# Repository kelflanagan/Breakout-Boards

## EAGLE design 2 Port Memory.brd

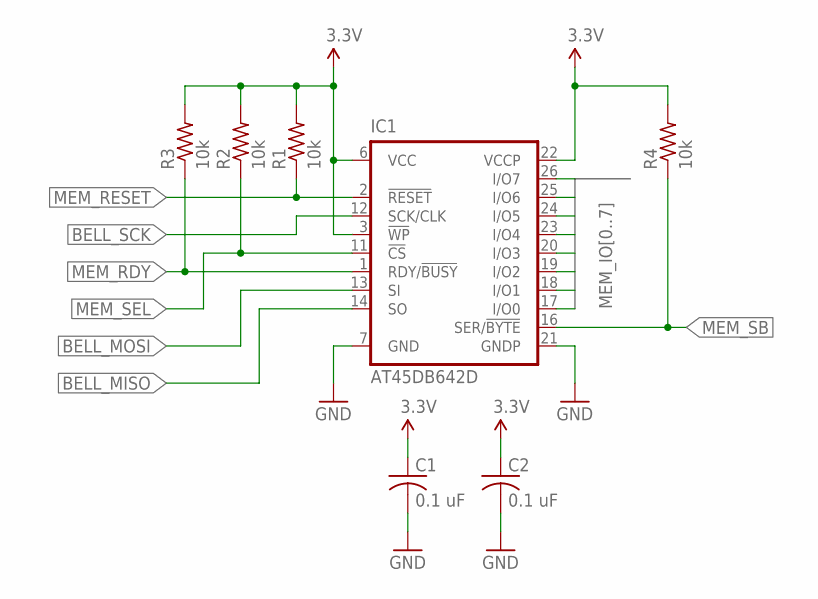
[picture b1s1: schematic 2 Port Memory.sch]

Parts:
C1, C2: 0.1 uF; 0603_CAP; DIGIKEY# 399-1096-1-ND
IC1: AT45DB642D; 28T-TSOP-1
R1, R2, R3, R4: 10k; 0603_RESISTOR; DIGIKEY# P10KGCT-ND

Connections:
3.3V: C1.1, C2.1, IC1.3 (!WP), IC1.6 (VCC), IC1.22 (VCCP), R1.2, R2.2, R3.2, R4.2
BELL_MISO: IC1.14 (SO)
BELL_MOSI: IC1.13 (SI)
BELL_SCK: IC1.12 (SCK/CLK)
GND: C1.2, C2.2, IC1.7 (GND), IC1.21 (GNDP)
MEM_IO0: IC1.17 (I/O0)
MEM_IO1: IC1.18 (I/O1)
MEM_IO2: IC1.19 (I/O2)
MEM_IO3: IC1.20 (I/O3)
MEM_IO4: IC1.23 (I/O4)
MEM_IO5: IC1.24 (I/O5)
MEM_IO6: IC1.25 (I/O6)
MEM_IO7: IC1.26 (I/O7)
MEM_RDY: IC1.1 (RDY/!BUSY), R3.1
MEM_RESET: IC1.2 (!RESET), R1.1
MEM_SB: IC1.16 (SER/!BYTE), R4.1
MEM_SEL: IC1.11 (!CS), R2.1

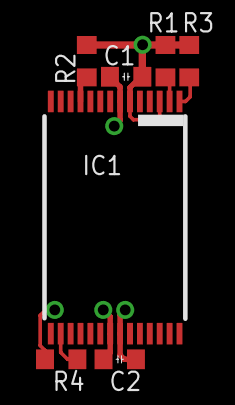
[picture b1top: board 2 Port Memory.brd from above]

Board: 4 copper layers, 7 parts (0 on the bottom side), 6 nets.

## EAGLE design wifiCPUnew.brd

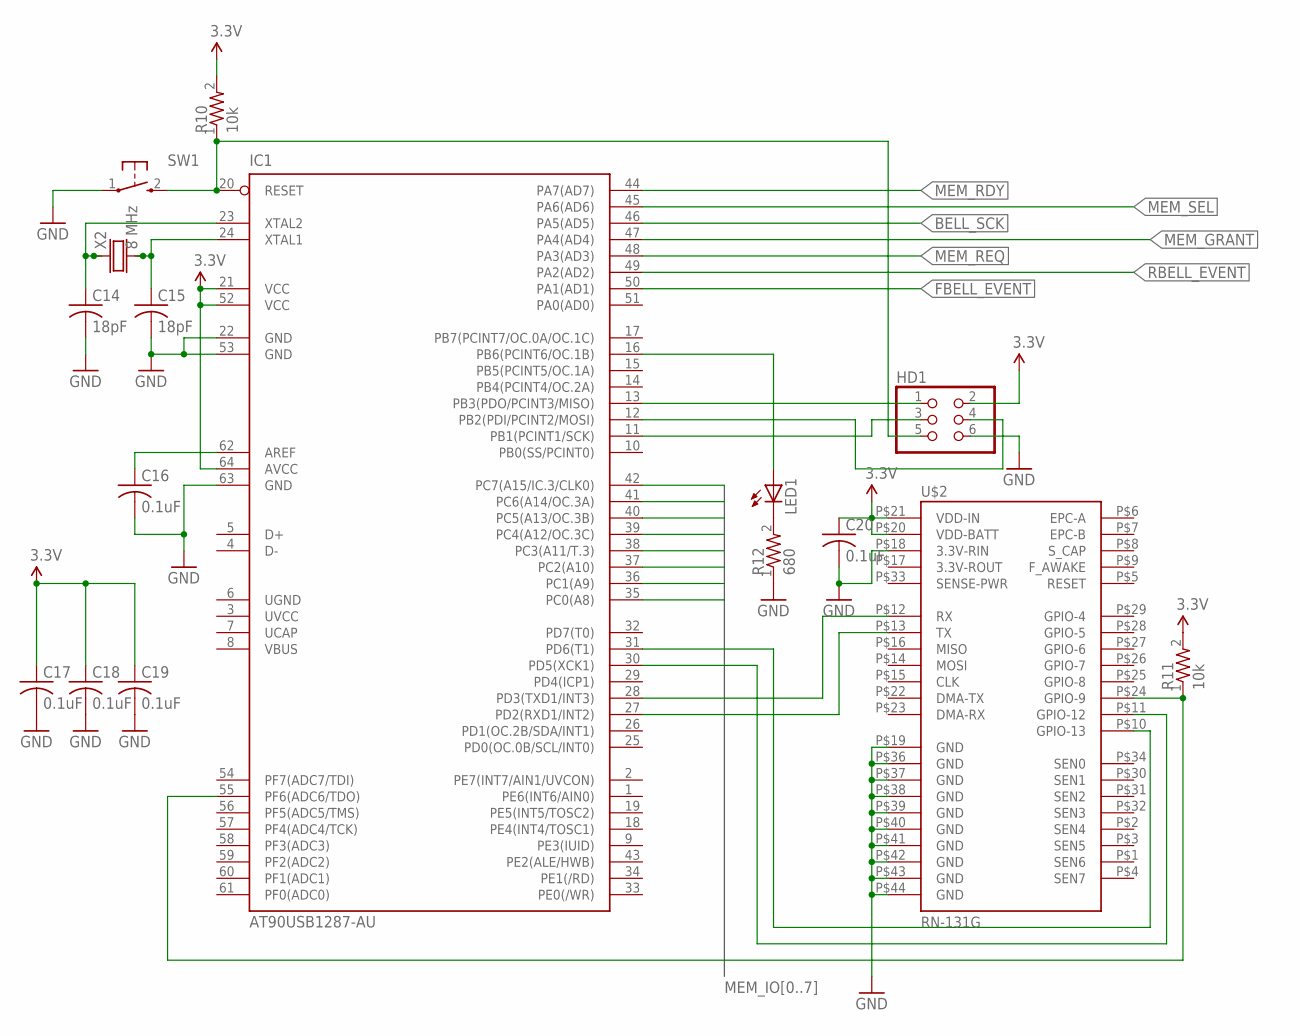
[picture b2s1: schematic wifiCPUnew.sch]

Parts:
C14, C15: 18pF; 0603_RESISTOR
C16, C17, C18, C19, C20: 0.1uF; 0603_RESISTOR
HD1: HEADER2X3
IC1: AT90USB1287-AU; TQFP64
LED1: LEDCHIP-LED0603; CHIP-LED0603
R10, R11: 10k; 0603_RESISTOR
R12: 680; 0603_RESISTOR
SW1: TAC-SWITCH
U$2: RN-131G
X2: 8 MHz; CRYSTAL_5X3

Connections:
3.3V: C17.1, C18.1, C19.1, C20.1, HD1.2, IC1.21 (VCC), IC1.52 (VCC), IC1.64 (AVCC), R10.2, R11.2, U$2.P$20 (VDD-BATT), U$2.P$21 (VDD-IN)
BELL_SCK: IC1.46 (PA5(AD5))
FBELL_EVENT: IC1.50 (PA1(AD1))
GND: C14.2, C15.2, C16.2, C17.2, C18.2, C19.2, C20.2, HD1.6, IC1.22 (GND), IC1.53 (GND), IC1.63 (GND), R12.1, SW1.1, U$2.P$18 (3.3V-RIN), U$2.P$19 (GND), U$2.P$36 (GND), U$2.P$37 (GND), U$2.P$38 (GND), U$2.P$39 (GND), U$2.P$40 (GND), U$2.P$41 (GND), U$2.P$42 (GND), U$2.P$43 (GND), U$2.P$44 (GND)
MEM_GRANT: IC1.47 (PA4(AD4))
MEM_IO0: IC1.35 (PC0(A8))
MEM_IO1: IC1.36 (PC1(A9))
MEM_IO2: IC1.37 (PC2(A10))
MEM_IO3: IC1.38 (PC3(A11/T.3))
MEM_IO4: IC1.39 (PC4(A12/OC.3C))
MEM_IO5: IC1.40 (PC5(A13/OC.3B))
MEM_IO6: IC1.41 (PC6(A14/OC.3A))
MEM_IO7: IC1.42 (PC7(A15/IC.3/CLK0))
MEM_RDY: IC1.44 (PA7(AD7))
MEM_REQ: IC1.48 (PA3(AD3))
MEM_SEL: IC1.45 (PA6(AD6))
MISO: HD1.1, IC1.13 (PB3(PDO/PCINT3/MISO))
MOSI: HD1.4, IC1.12 (PB2(PDI/PCINT2/MOSI))
unnamed: C14.1, IC1.23 (XTAL2), X2.1
unnamed: C15.1, IC1.24 (XTAL1), X2.2
unnamed: LED1.C, R12.2
unnamed: IC1.16 (PB6(PCINT6/OC.1B)), LED1.A
unnamed: IC1.28 (PD3(TXD1/INT3)), U$2.P$12 (RX)
unnamed: C16.1, IC1.62 (AREF)
unnamed: IC1.27 (PD2(RXD1/INT2)), U$2.P$13 (TX)
unnamed: IC1.31 (PD6(T1)), U$2.P$10 (GPIO-13)
unnamed: IC1.30 (PD5(XCK1)), U$2.P$11 (GPIO-12)
unnamed: IC1.55 (PF6(ADC6/TDO)), R11.1, U$2.P$24 (GPIO-9)
RBELL_EVENT: IC1.49 (PA2(AD2))
SCK: HD1.3, IC1.11 (PB1(PCINT1/SCK))
UCAP: IC1.7 (UCAP)
UGND: IC1.6 (UGND)
UVCC: IC1.3 (UVCC)
VBUS: IC1.8 (VBUS)
WIFI_RESET: HD1.5, IC1.20 (RESET), R10.1, SW1.2

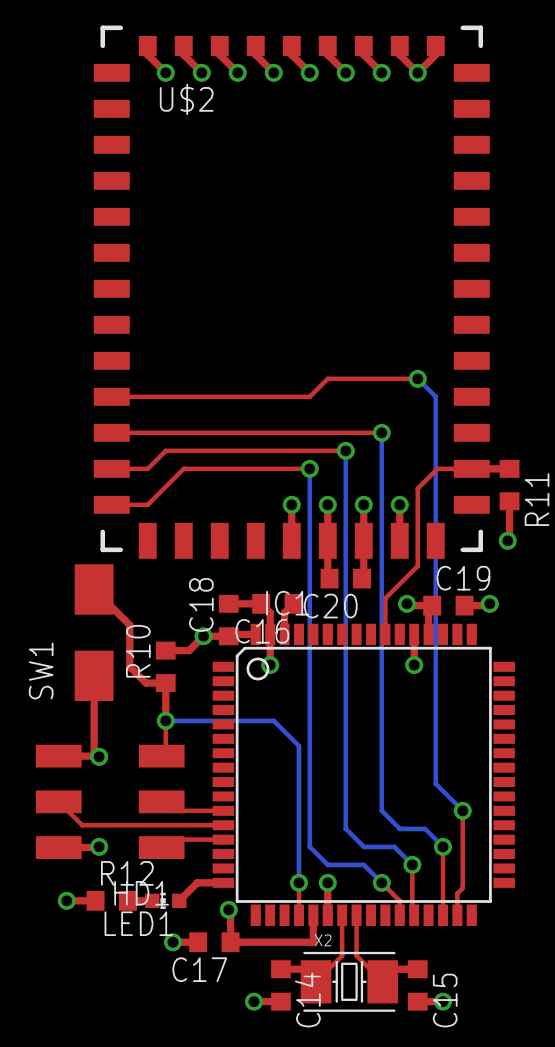
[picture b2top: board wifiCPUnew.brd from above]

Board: 4 copper layers, 16 parts (0 on the bottom side), 16 nets.

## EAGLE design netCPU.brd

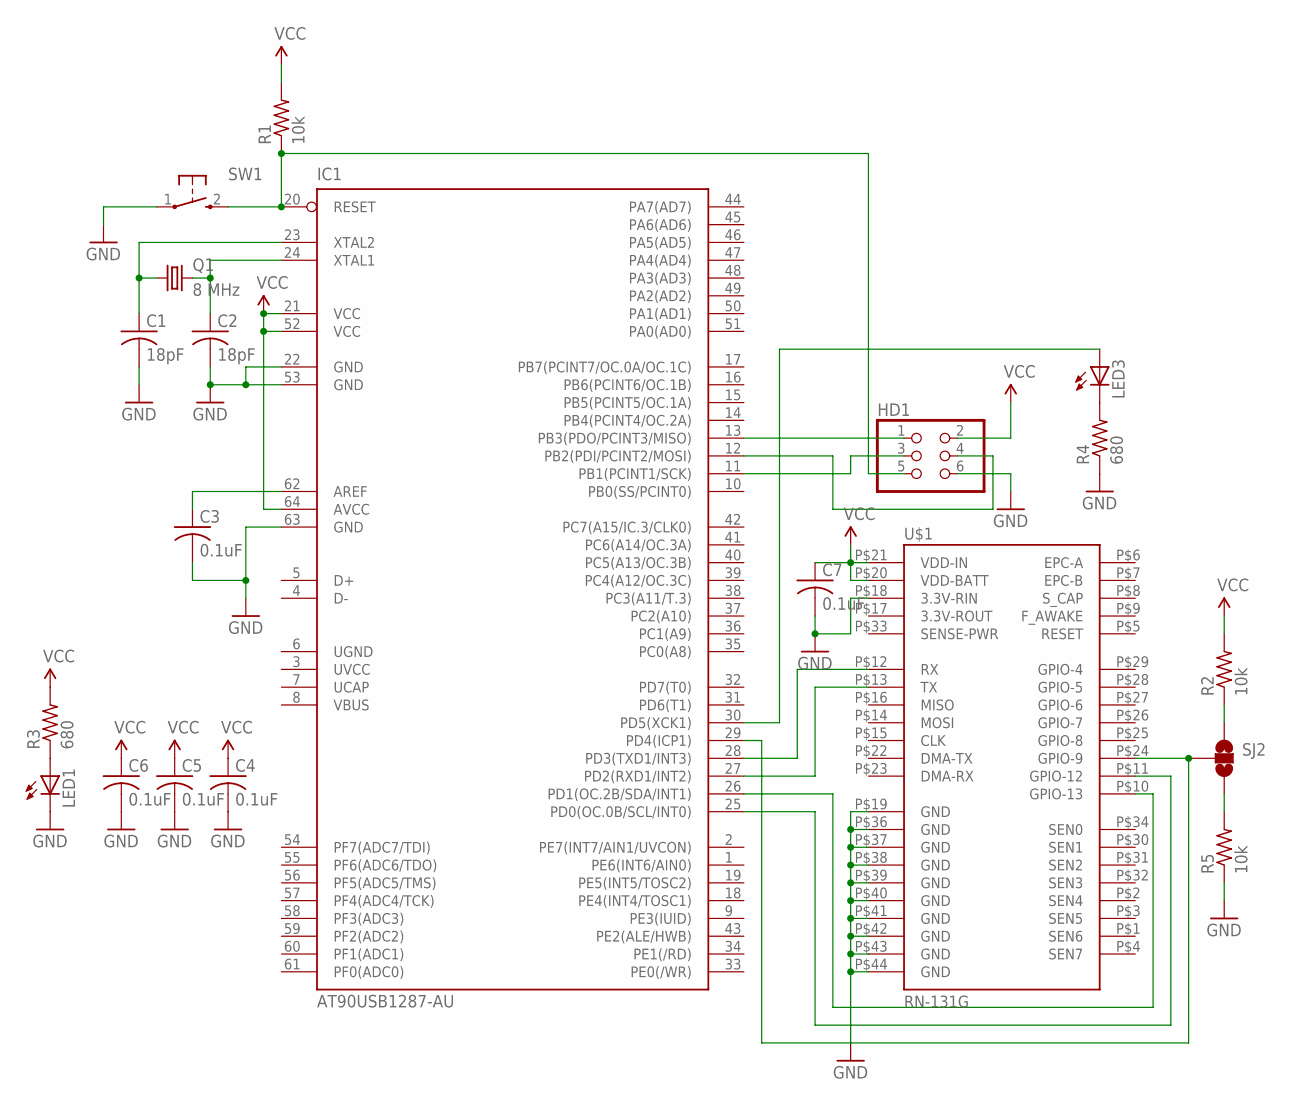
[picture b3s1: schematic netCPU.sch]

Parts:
C1, C2: 18pF; C0603K
C3, C4, C5, C6, C7: 0.1uF; C0603K
HD1: HEADER2X3
IC1: AT90USB1287-AU; TQFP64
LED1, LED3: LEDCHIP-LED0603; CHIP-LED0603
Q1: 8 MHz; HC49UP
R1, R2, R5: 10k; R0603
R3, R4: 680; R0603
SJ2: SOLDERJUMPER_2WAYPASTE2&3; SJ_3_PASTE2&3
SW1: TAC-SWITCH
U$1: RN-131G

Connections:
GND: C1.2, C2.2, C3.2, C4.2, C5.2, C6.2, C7.2, HD1.6, IC1.22 (GND), IC1.53 (GND), IC1.63 (GND), LED1.C, R4.1, R5.1, SW1.1, U$1.P$18 (3.3V-RIN), U$1.P$19 (GND), U$1.P$36 (GND), U$1.P$37 (GND), U$1.P$38 (GND), U$1.P$39 (GND), U$1.P$40 (GND), U$1.P$41 (GND), U$1.P$42 (GND), U$1.P$43 (GND), U$1.P$44 (GND)
unnamed: C1.1, IC1.23 (XTAL2), Q1.1
unnamed: C2.1, IC1.24 (XTAL1), Q1.2
unnamed: HD1.1, IC1.13 (PB3(PDO/PCINT3/MISO))
unnamed: HD1.5, IC1.20 (RESET), R1.1, SW1.2
unnamed: HD1.4, IC1.12 (PB2(PDI/PCINT2/MOSI))
unnamed: IC1.28 (PD3(TXD1/INT3)), U$1.P$12 (RX)
unnamed: HD1.3, IC1.11 (PB1(PCINT1/SCK))
unnamed: C3.1, IC1.62 (AREF)
unnamed: IC1.27 (PD2(RXD1/INT2)), U$1.P$13 (TX)
unnamed: IC1.26 (PD1(OC.2B/SDA/INT1)), U$1.P$10 (GPIO-13)
unnamed: IC1.25 (PD0(OC.0B/SCL/INT0)), U$1.P$11 (GPIO-12)
unnamed: LED1.A, R3.1
unnamed: IC1.29 (PD4(ICP1)), SJ2.2, U$1.P$24 (GPIO-9)
unnamed: LED3.C, R4.2
unnamed: IC1.30 (PD5(XCK1)), LED3.A
unnamed: R5.2, SJ2.3
unnamed: R2.1, SJ2.1
UCAP: IC1.7 (UCAP)
UGND: IC1.6 (UGND)
UVCC: IC1.3 (UVCC)
VBUS: IC1.8 (VBUS)
VCC: C4.1, C5.1, C6.1, C7.1, HD1.2, IC1.21 (VCC), IC1.52 (VCC), IC1.64 (AVCC), R1.2, R2.2, R3.2, U$1.P$20 (VDD-BATT), U$1.P$21 (VDD-IN)

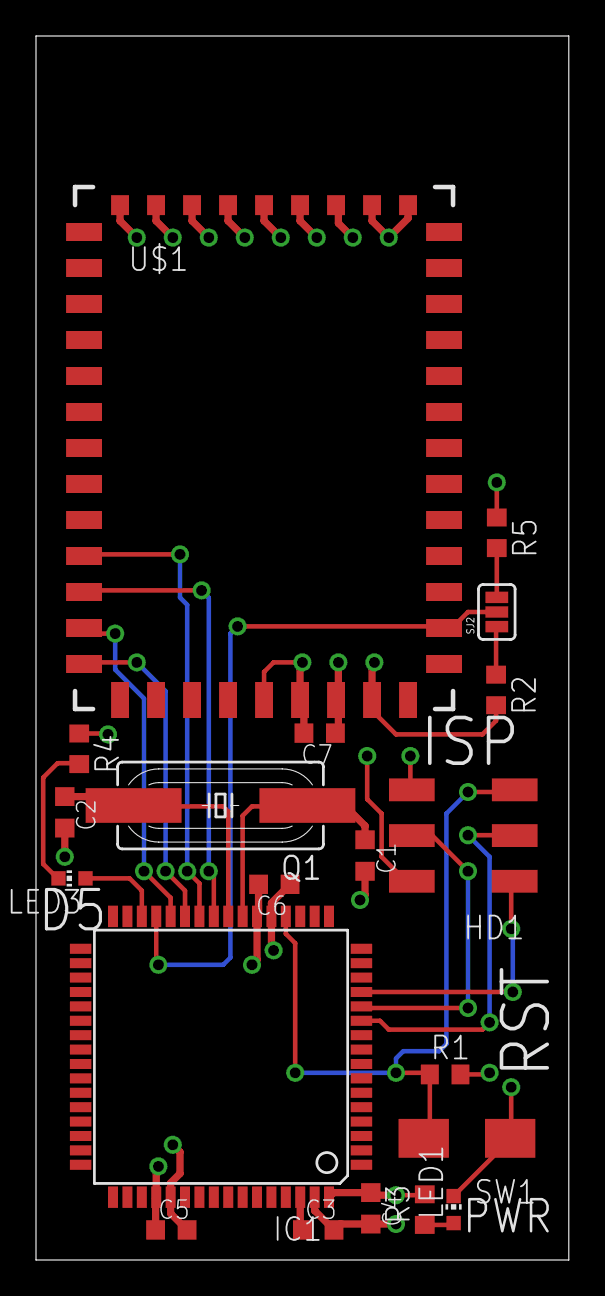
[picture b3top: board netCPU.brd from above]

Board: 4 copper layers, 29.6 x 68.0 mm, 20 parts (0 on the bottom side), 19 nets.

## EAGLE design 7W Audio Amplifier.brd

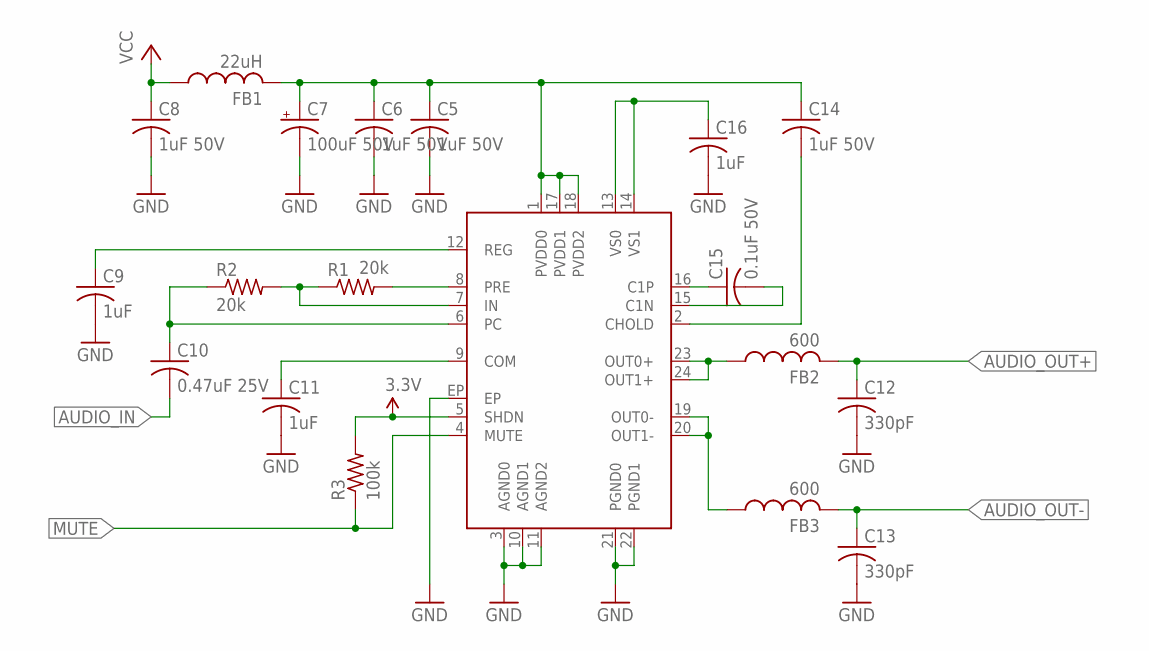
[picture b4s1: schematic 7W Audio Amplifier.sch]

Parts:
C5, C6, C8, C14: 1uF 50V; 0805_CAP; DIGIKEY# 445-7547-1-ND
C7: 100uF 50V; F_CAP; DIGIKEY# PCE3917CT-ND
C9, C11, C16: 1uF; 0603_CAP; DIGIKEY# 445-5138-1-ND
C10: 0.47uF 25V; 0603_CAP; DIGIKEY# 445-7418-1-ND
C12, C13: 330pF; 0603_CAP; DIGIKEY# 445-5074-1-ND
C15: 0.1uF 50V; 0603_CAP; DIGIKEY# 445-1314-1-ND
FB1: 22uH; 0805_FB; DIGIKEY# 490-5987-1-ND
FB2, FB3: 600; 0805_FB; DIGIKEY# 445-2206-1-ND
MAX1: MAX9737; TQFN24
R1, R2: 20k; 0603_RESISTOR; DIGIKEY# RHM20.0KCFCT-ND
R3: 100k; 0603_RESISTOR; DIGIKEY# 311-100KGRCT-ND

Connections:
3.3V: MAX1.5 (SHDN), R3.2
AUDIO_IN: C10.2
AUDIO_OUT+: C12.1, FB2.2
AUDIO_OUT-: C13.1, FB3.2
GND: C5.2, C6.2, C7.-, C8.2, C9.2, C11.2, C12.2, C13.2, C16.2, MAX1.3 (AGND0), MAX1.10 (AGND1), MAX1.11 (AGND2), MAX1.21 (PGND0), MAX1.22 (PGND1), MAX1.EP
MUTE: MAX1.4 (MUTE), R3.1
unnamed: C9.1, MAX1.12 (REG)
unnamed: MAX1.8 (PRE), R1.2
unnamed: C5.1, C6.1, C7.+, C14.1, FB1.2, MAX1.1 (PVDD0), MAX1.17 (PVDD1), MAX1.18 (PVDD2)
unnamed: MAX1.7 (IN), R1.1, R2.2
unnamed: C10.1, MAX1.6 (PC), R2.1
unnamed: C11.1, MAX1.9 (COM)
unnamed: C14.2, MAX1.2 (CHOLD)
unnamed: C15.1, MAX1.16 (C1P)
unnamed: C15.2, MAX1.15 (C1N)
unnamed: C16.1, MAX1.13 (VS0), MAX1.14 (VS1)
unnamed: FB3.1, MAX1.19 (OUT0-), MAX1.20 (OUT1-)
unnamed: FB2.1, MAX1.23 (OUT0+), MAX1.24 (OUT1+)
VCC: C8.1, FB1.1

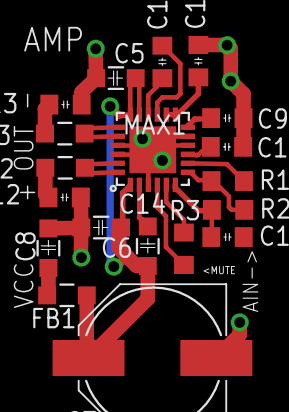
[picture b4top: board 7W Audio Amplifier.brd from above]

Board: 4 copper layers, 19 parts (0 on the bottom side), 18 nets.

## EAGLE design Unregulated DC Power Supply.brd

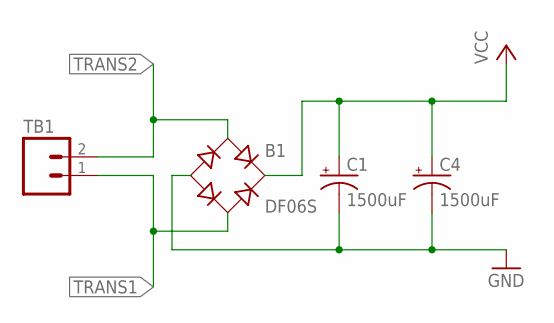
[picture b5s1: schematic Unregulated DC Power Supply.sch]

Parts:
B1: DF06S; DFS
C1, C4: 1500uF; CAP_J16
TB1: TERMINAL_BLOCK_2; TERMINL_BLOCK_2_POS

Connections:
GND: B1.-, C1.1 (-), C4.1 (-)
TRANS1: B1.AC2, TB1.1
TRANS2: B1.AC1, TB1.2
VCC: B1.+, C1.2 (+), C4.2 (+)

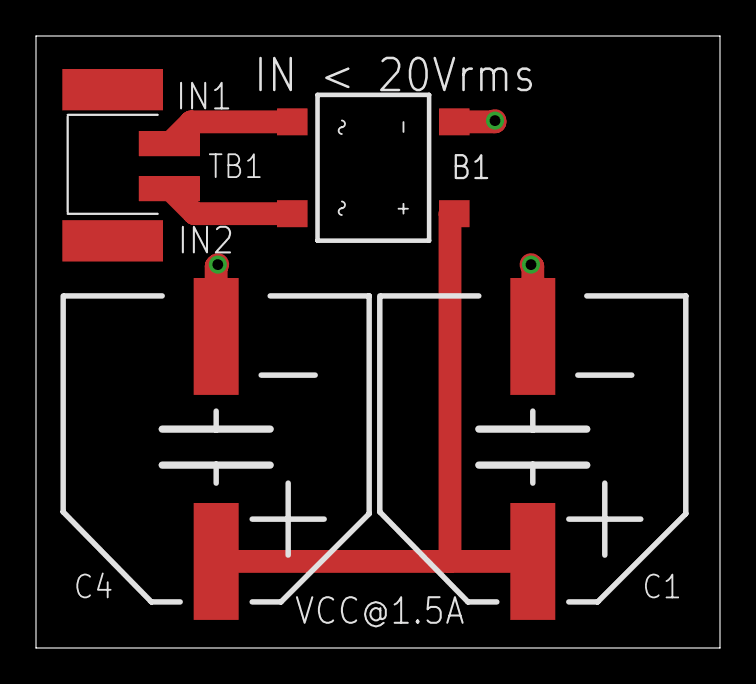
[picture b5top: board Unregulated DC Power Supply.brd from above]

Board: 4 copper layers, 38.0 x 34.0 mm, 4 parts (0 on the bottom side), 4 nets.

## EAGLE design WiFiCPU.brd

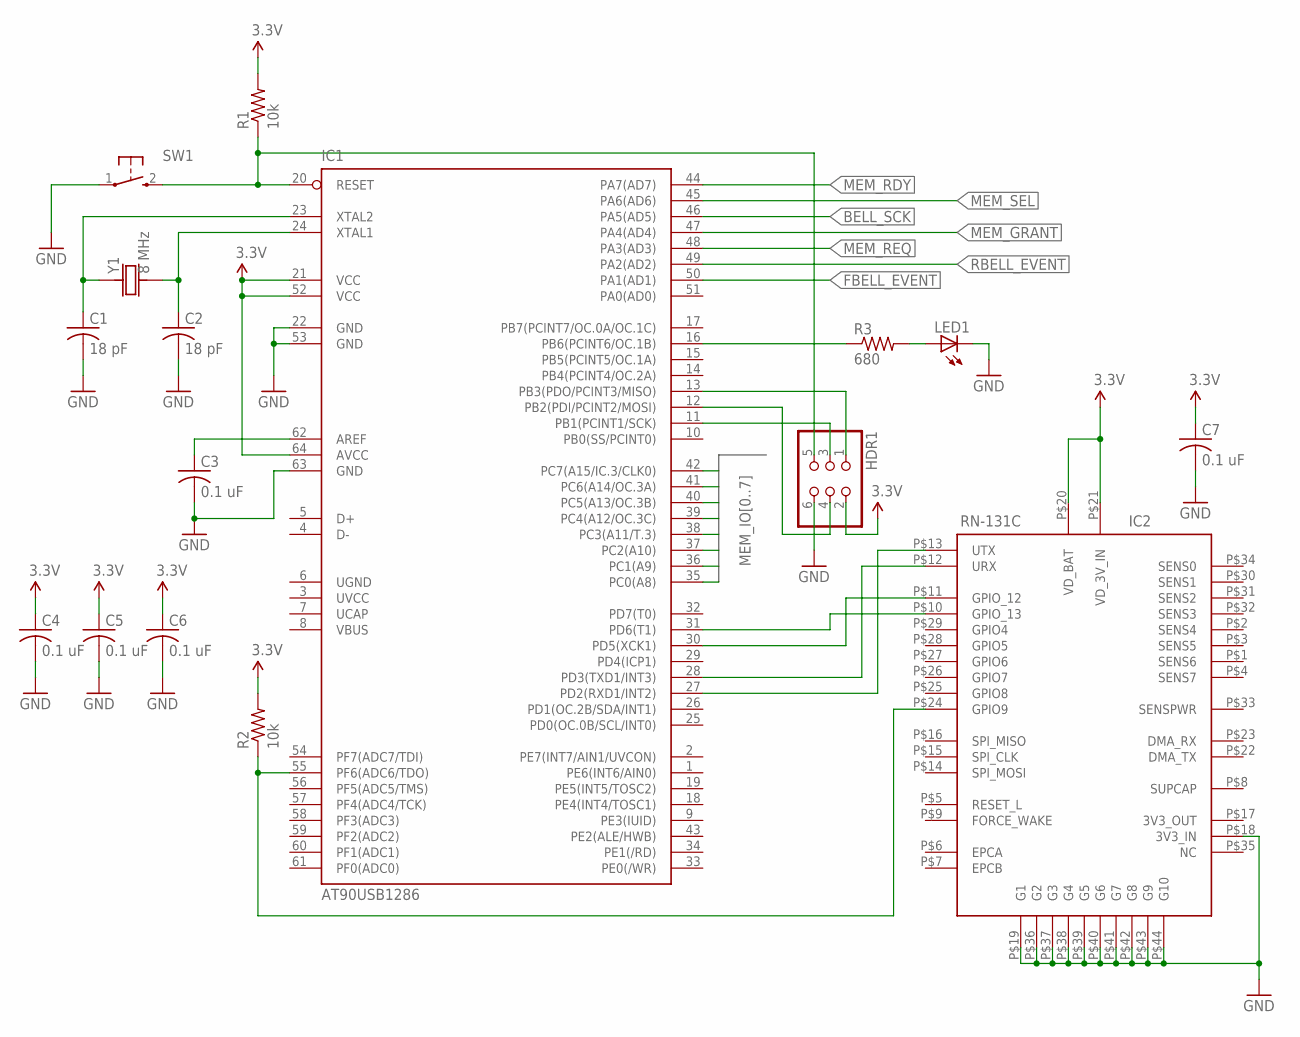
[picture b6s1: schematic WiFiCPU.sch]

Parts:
C1, C2: 18 pF; 0603_CAP; DIGIKEY# 399-1052-1-ND
C3, C4, C5, C6, C7: 0.1 uF; 0603_CAP; DIGIKEY# 399-1096-1-ND
HDR1: HEADER_2X3
IC1: AT90USB1286; TQFP64; DIGIKEY# AT90USB1286-AURCT-ND
IC2: RN-131C; RN-131G
LED1: LED0603; 0603_LED
R1, R2: 10k; 0603_RESISTOR; DIGIKEY# P10KGCT-ND
R3: 680; 0603_RESISTOR; DIGIKEY# P680GCT-ND
SW1: SWITCH; SWITCH_TAC
Y1: 8 MHz; CRYSTAL_5X3; DIGIKEY# 887-1448-1-ND

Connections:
3.3V: C4.1, C5.1, C6.1, C7.1, HDR1.2, IC1.21 (VCC), IC1.52 (VCC), IC1.64 (AVCC), IC2.P$20 (VD_BAT), IC2.P$21 (VD_3V_IN), R1.2, R2.2
BELL_SCK: IC1.46 (PA5(AD5))
FBELL_EVENT: IC1.50 (PA1(AD1))
GND: C1.2, C2.2, C3.2, C4.2, C5.2, C6.2, C7.2, HDR1.6, IC1.22 (GND), IC1.53 (GND), IC1.63 (GND), IC2.P$18 (3V3_IN), IC2.P$19 (G1), IC2.P$36 (G2), IC2.P$37 (G3), IC2.P$38 (G4), IC2.P$39 (G5), IC2.P$40 (G6), IC2.P$41 (G7), IC2.P$42 (G8), IC2.P$43 (G9), IC2.P$44 (G10), LED1.C, SW1.1
MEM_GRANT: IC1.47 (PA4(AD4))
MEM_IO0: IC1.35 (PC0(A8))
MEM_IO1: IC1.36 (PC1(A9))
MEM_IO2: IC1.37 (PC2(A10))
MEM_IO3: IC1.38 (PC3(A11/T.3))
MEM_IO4: IC1.39 (PC4(A12/OC.3C))
MEM_IO5: IC1.40 (PC5(A13/OC.3B))
MEM_IO6: IC1.41 (PC6(A14/OC.3A))
MEM_IO7: IC1.42 (PC7(A15/IC.3/CLK0))
MEM_RDY: IC1.44 (PA7(AD7))
MEM_REQ: IC1.48 (PA3(AD3))
MEM_SEL: IC1.45 (PA6(AD6))
unnamed: C1.1, IC1.23 (XTAL2), Y1.1
unnamed: C2.1, IC1.24 (XTAL1), Y1.2
unnamed: IC1.28 (PD3(TXD1/INT3)), IC2.P$12 (URX)
unnamed: IC1.27 (PD2(RXD1/INT2)), IC2.P$13 (UTX)
unnamed: C3.1, IC1.62 (AREF)
unnamed: IC1.30 (PD5(XCK1)), IC2.P$11 (GPIO_12)
unnamed: IC1.31 (PD6(T1)), IC2.P$10 (GPIO_13)
unnamed: IC1.55 (PF6(ADC6/TDO)), IC2.P$24 (GPIO9), R2.1
unnamed: HDR1.1, IC1.13 (PB3(PDO/PCINT3/MISO))
unnamed: HDR1.4, IC1.12 (PB2(PDI/PCINT2/MOSI))
unnamed: HDR1.3, IC1.11 (PB1(PCINT1/SCK))
unnamed: IC1.16 (PB6(PCINT6/OC.1B)), R3.1
unnamed: LED1.A, R3.2
RBELL_EVENT: IC1.49 (PA2(AD2))
UCAP: IC1.7 (UCAP)
UGND: IC1.6 (UGND)
UVCC: IC1.3 (UVCC)
VBUS: IC1.8 (VBUS)
WIFI_RESET: HDR1.5, IC1.20 (RESET), R1.1, SW1.2

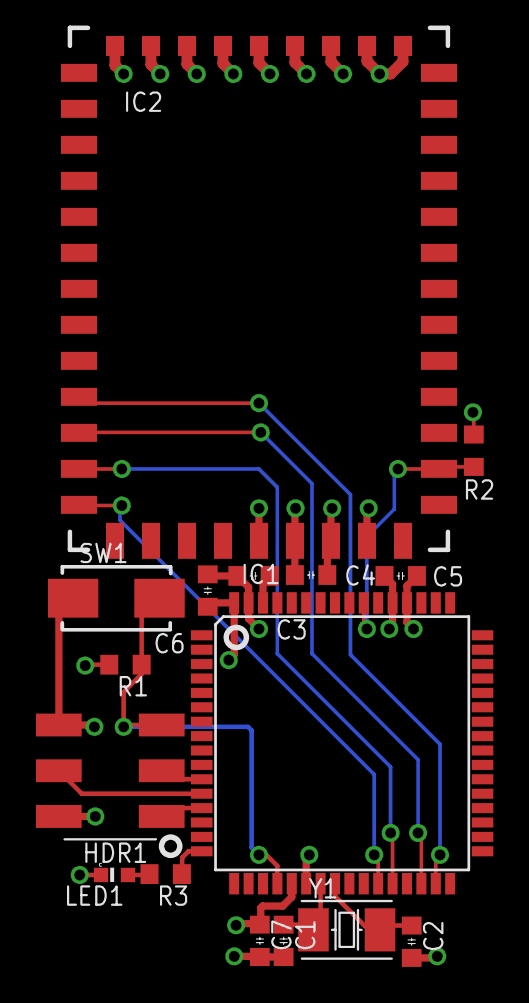
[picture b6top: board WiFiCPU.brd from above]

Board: 4 copper layers, 16 parts (0 on the bottom side), 16 nets.

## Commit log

2016-05-04 Frist commit

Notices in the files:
parts and their libraries:
SparkFun-Aesthetics: Licensing: CC v3.0 Share-Alike You are welcome to use this library for commercial purposes.
